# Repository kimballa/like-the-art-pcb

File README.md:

You Don't Have to Like All the Art! -- PCBs
===========================================

PCB designs and eCAD files for the "You Don't Have to Like All the Art!" project.

This system consists of two distinct circuit boards:

* `lta-logic-module` - The "logic" that determines when it's dark out / should be active, what
  messages to light up on the sign, manages PWM or other effects when displaying the sign, and
  also handles button inputs from users. Runs on a combination of 5V and 3V3. This is designed
  around a port for installing an Adafruit Feather M4 Express (ATSAMD51 / Cortex-M4) Arduino
  device. The rest of the circuitry:
  * Provides regulated 5V0 input voltage for the rest of this module
  * Manages a wide fanout of control and sense lines via I2C
  * Uses a phototransistor to sense when it is dark out, and thus the system should be active
    vs in standby mode
  * Combines the sign control lines with a global PWM signal and buffers the output before feeding
    to the power module.
* `lta-power-module` - The high-power circuits that actually drive the LED signs. This module is
  "dumb" and contains no combinational logic or more complex circuitry. Most of the board is used
  for mounting 3rd-party PCB submodules for high-amp 12V0 voltage regulation, distributing a
  power bus, and actually driving power MOSFETs linked to each sign's power wiring. The onboard
  circuitry:
  * Provides regulated 5V0 input voltage for the rest of the onboard circuitry
  * Displays condition of regulated 12V0 input power
  * Uses SN75374 low-side drivers to send control signals to the MOSFET modules
  * Contains a small integrated protoboard for in-field repairs and modifications

The `photodiode-sim` subproject is a simplified version of the `DARK` detection circuitry for use
with `ngspice` to understand the sensitivity of the logic signal to input current levels from the
phototransistor and the variable resistance of the potentiometer used as an in-field sensitivity
calibration input.

A third PCB (`mosfet-chip`) is a mini-PCB to connect two circuits via screw-terminals, switchable by
an onboard `IRLZ24` NMOS FET transistor activated by a separate gate pin. 16 of these are mounted on
the power module by #0 machine screws.

I originally used this
[High-Power Dual MOSFET Switch Module](https://protosupplies.com/product/high-power-dual-mosfet-switch-module/)
but found the screw terminals included were too unreliable. This PCB is footprint-compatible and
uses larger-gauge, higher-quality terminal blocks by Phoenix Contact. The `mosfet-chip/` directory
includes a panelized (2x3) layout suitable for PCBA and the BOM to enable assembly at JLCPCB.

Fabrication
-----------

All models are built with KiCAD 6. Each module contains a BOM spreadsheet for assembly with MPNs to
order from DigiKey or elsewhere as noted. Per-run fabrication gerbers are kept in versioned
subdirectories of each submodule project.

All modules are fabricated with the following parameters:

* 2 layers
* 1.6mm finished board thickness
* FR4-Tg130 core
* Both layers 1 oz copper thickness
* Blue soldermask, white silkscreen (these choices made only for aesthetic reasons and do not
  affect eng or mfg)

The logic module is fabricated with ENIG finish for reflow; the power module can be finished
with RoHS Pb-free HASL.

The logic module was fabricated by Elecrow and follows their design rules. Smallest
traces are 0.20mm. All trace separation >= 0.15mm.

The power module was fabricated by JLCPCB and follows their design rules. Smallest power module
traces and trace separations are 0.25mm / 0.20mm, which more than meets their capabilities.

Assembly
--------

Boards require only single-sided assembly.

The logic module is a mixed SMD/THT board and was assembled by Elecrow. Smallest reflow components
are 0603. Logic module ICs are SOIC (1.27mm pitch). Actual LEDs, resistors, and IC decoupling
capacitors do not follow the BOM strictly but instead use house parts (except as noted `Exact MPN
Only` in the BOM). More notes about logic module assembly are in `README-fab-and-pcba.txt` in
the logic module directory.

The power module is THT-only and intended for hand-soldered assembly. (A single 7343-metric / 2917
/ "size D" tantalum SMD capacitor for the 5V0 regulator can also be hand-soldered.)

The mosfet chips are a mixed SMD/THT assembly and were assembled by JLCPCB. BOM includes SPNs
for JLC's preferred supplier. Individual mini-PCBs are too small for automated SMD assembly,
so gerbers are supplied for a panelized 2x3 PCB layout, made with the Panelizer plugin for KiCAD 6.

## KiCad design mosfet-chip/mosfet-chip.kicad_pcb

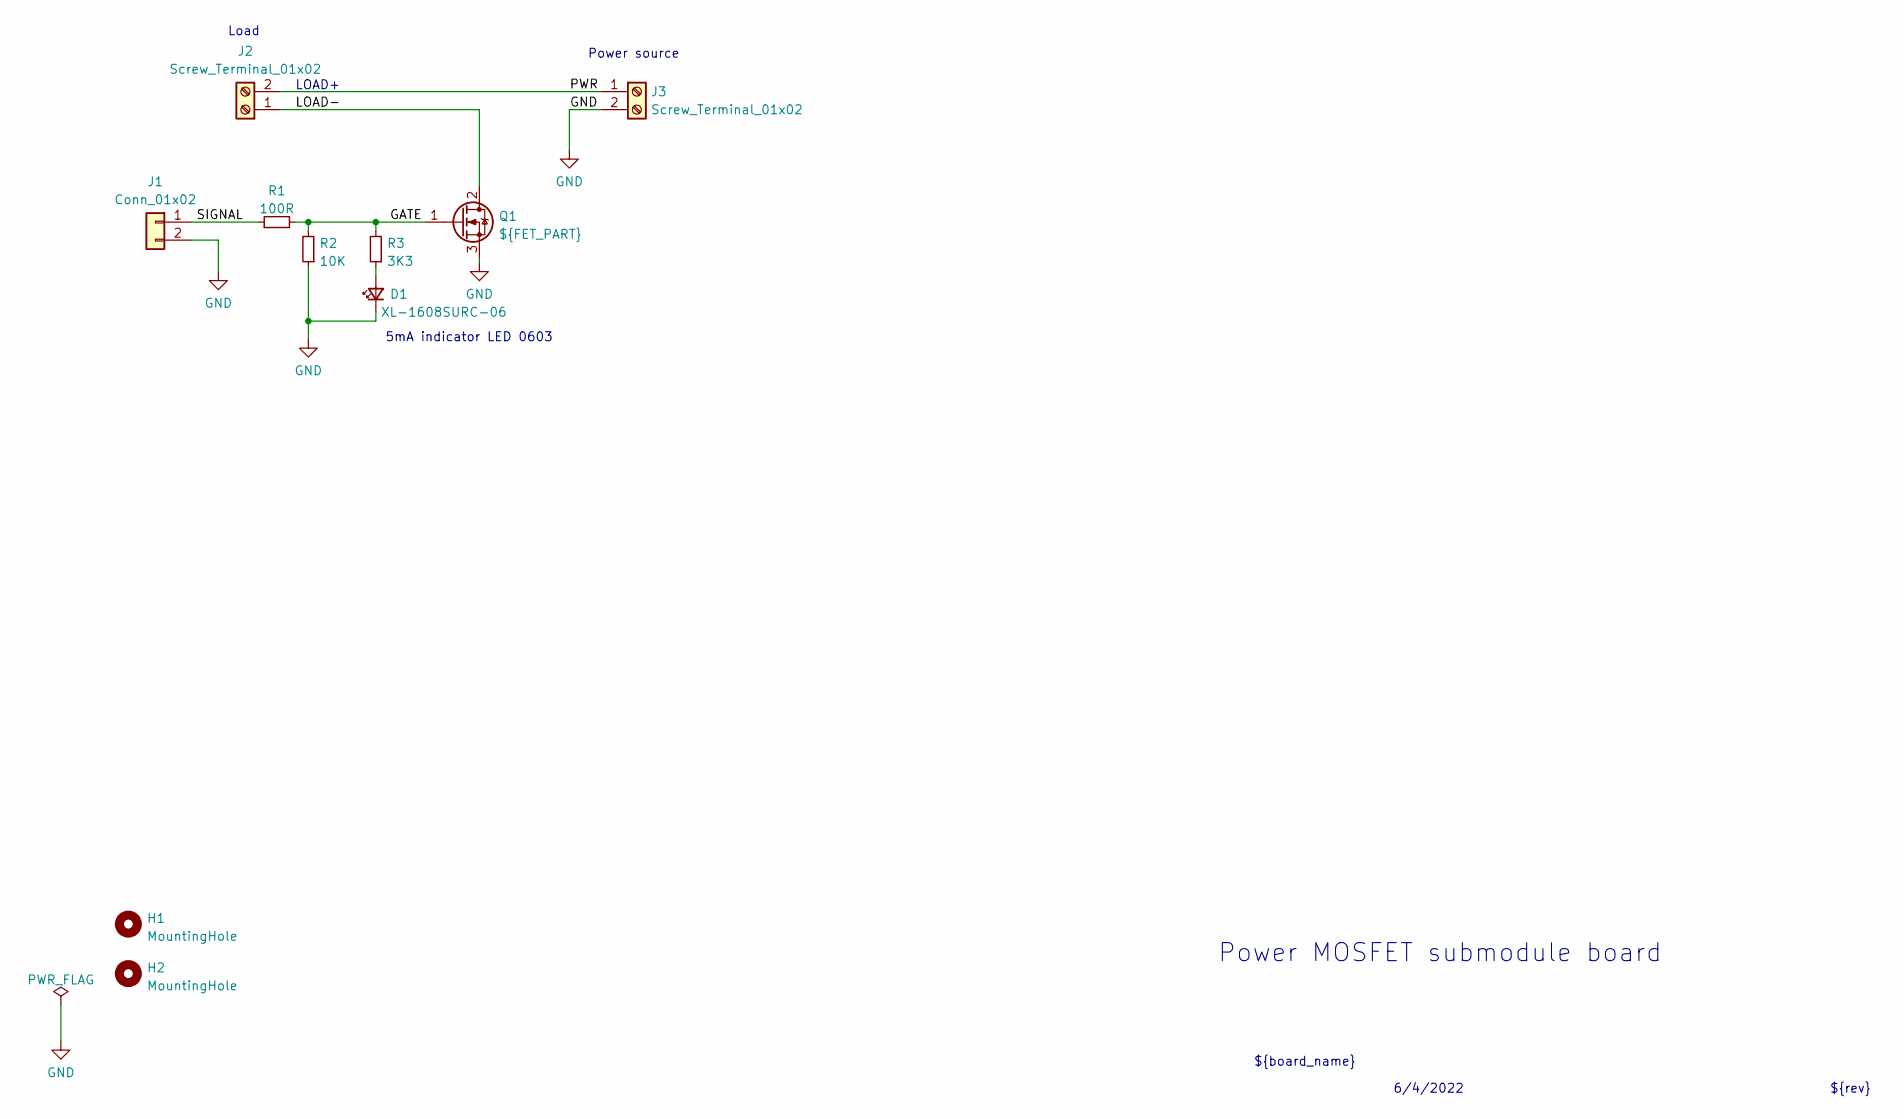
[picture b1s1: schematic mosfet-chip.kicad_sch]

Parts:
D1: XL-1608SURC-06; LED_0603_1608Metric; MPN XL-1608SURC-06; JLCPCB_PN C965799
H1, H2: MountingHole; MountingHole_80mil
J1: Conn_01x02; PinHeader_1x02_P2.54mm_Vertical; MPN 5-146858-1; JLCPCB_PN DNP
J2, J3: Screw_Terminal_01x02; Phoenix_1x02_1711725; MPN 1711725; JLCPCB_PN C89120
Q1: ${FET_PART}; TO-220-3_Vertical; MPN IRLZ34NPbF; JLCPCB_PN C513144
R1: 100R; R_0603_1608Metric; MPN 0603WAF1000T5E; JLCPCB_PN C22775
R2: 10K; R_0603_1608Metric; MPN 0603WAF1002T5E; JLCPCB_PN C25804
R3: 3K3; R_0603_1608Metric; MPN 0603WAF3301T5E; JLCPCB_PN C22978

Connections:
/GATE: Q1.1 (G), R1.2, R2.2, R3.2
/LOAD-: J2.1, Q1.2 (D)
/PWR: J2.2, J3.1
/SIGNAL: J1.1, R1.1
GND: D1.1 (K), J1.2, J3.2, Q1.3 (S), R2.1
unnamed: D1.2 (A), R3.1

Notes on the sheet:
Load
Power MOSFET submodule board
5mA indicator LED 0603
${rev}
LOAD+
${board_name}
6/4/2022
Power source

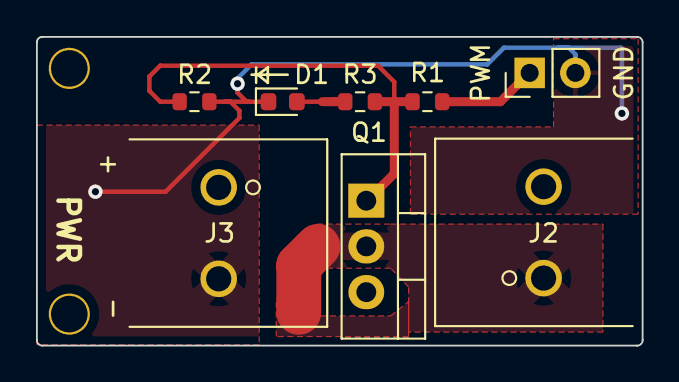
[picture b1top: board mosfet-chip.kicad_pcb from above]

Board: 2 copper layers, 33.6 x 17.1 mm, 10 parts (0 on the bottom side), 6 nets.

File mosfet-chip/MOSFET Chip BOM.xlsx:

Reference | Value | Footprint | Datasheet | Comment | JLCPCB_PN | MANUFACTURER | MPN | SPN | Qty
D1 | XL-1608SURC-06 | LED_SMD:LED_0603_1608Metric | https://datasheet.lcsc.com/lcsc/2012301032_XINGLIGHT-XL-1608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 |  | C965799 | XINGLIGHT | XL-1608SURC-06 |  | 1
> H1, H2 | MountingHole | Aaron_Pads:MountingHole_80mil | ~ |  |  |  |  |  | 2
J1 | Conn_01x02 | Connector_PinHeader_2.54mm:PinHeader_1x02_P2.54mm_Vertical | ~ | 0.1" gold male header pins | DNP | TE Connectivity AMP Connectors | 5-146858-1 | A105469CT-ND | 1
> J2, J3 | Screw_Terminal_01x02 | Aaron_Phoenix_Parts:Phoenix_1x02_1711725 | https://media.digikey.com/pdf/Data%20Sheets/Phoenix%20Contac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 |  | C89120 | Phoenix Contact | 1711725 | 277-1027-ND | 2
Q1 | ${FET_PART} | Package_TO_SOT_THT:TO-220-3_Vertical | https://www.infineon.com/dgdl/irlz34npbf.pdf?fileId=5546d462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 |  | C513144 | Infineon | IRLZ34NPbF | IRLZ34NPBF-ND | 1
R1 | 100R | Resistor_SMD:R_0603_1608Metric |  | 100R 1% 1/10W | C22775 | UNI-ROYAL | 0603WAF1000T5E |  | 1
R2 | 10K | Resistor_SMD:R_0603_1608Metric |  | 10K 1% 1/10W | C25804 | UNI-ROYAL | 0603WAF1002T5E |  | 1
R3 | 3K3 | Resistor_SMD:R_0603_1608Metric |  | 3K3 1% 1/10W | C22978 | UNI-ROYAL | 0603WAF3301T5E |  | 1

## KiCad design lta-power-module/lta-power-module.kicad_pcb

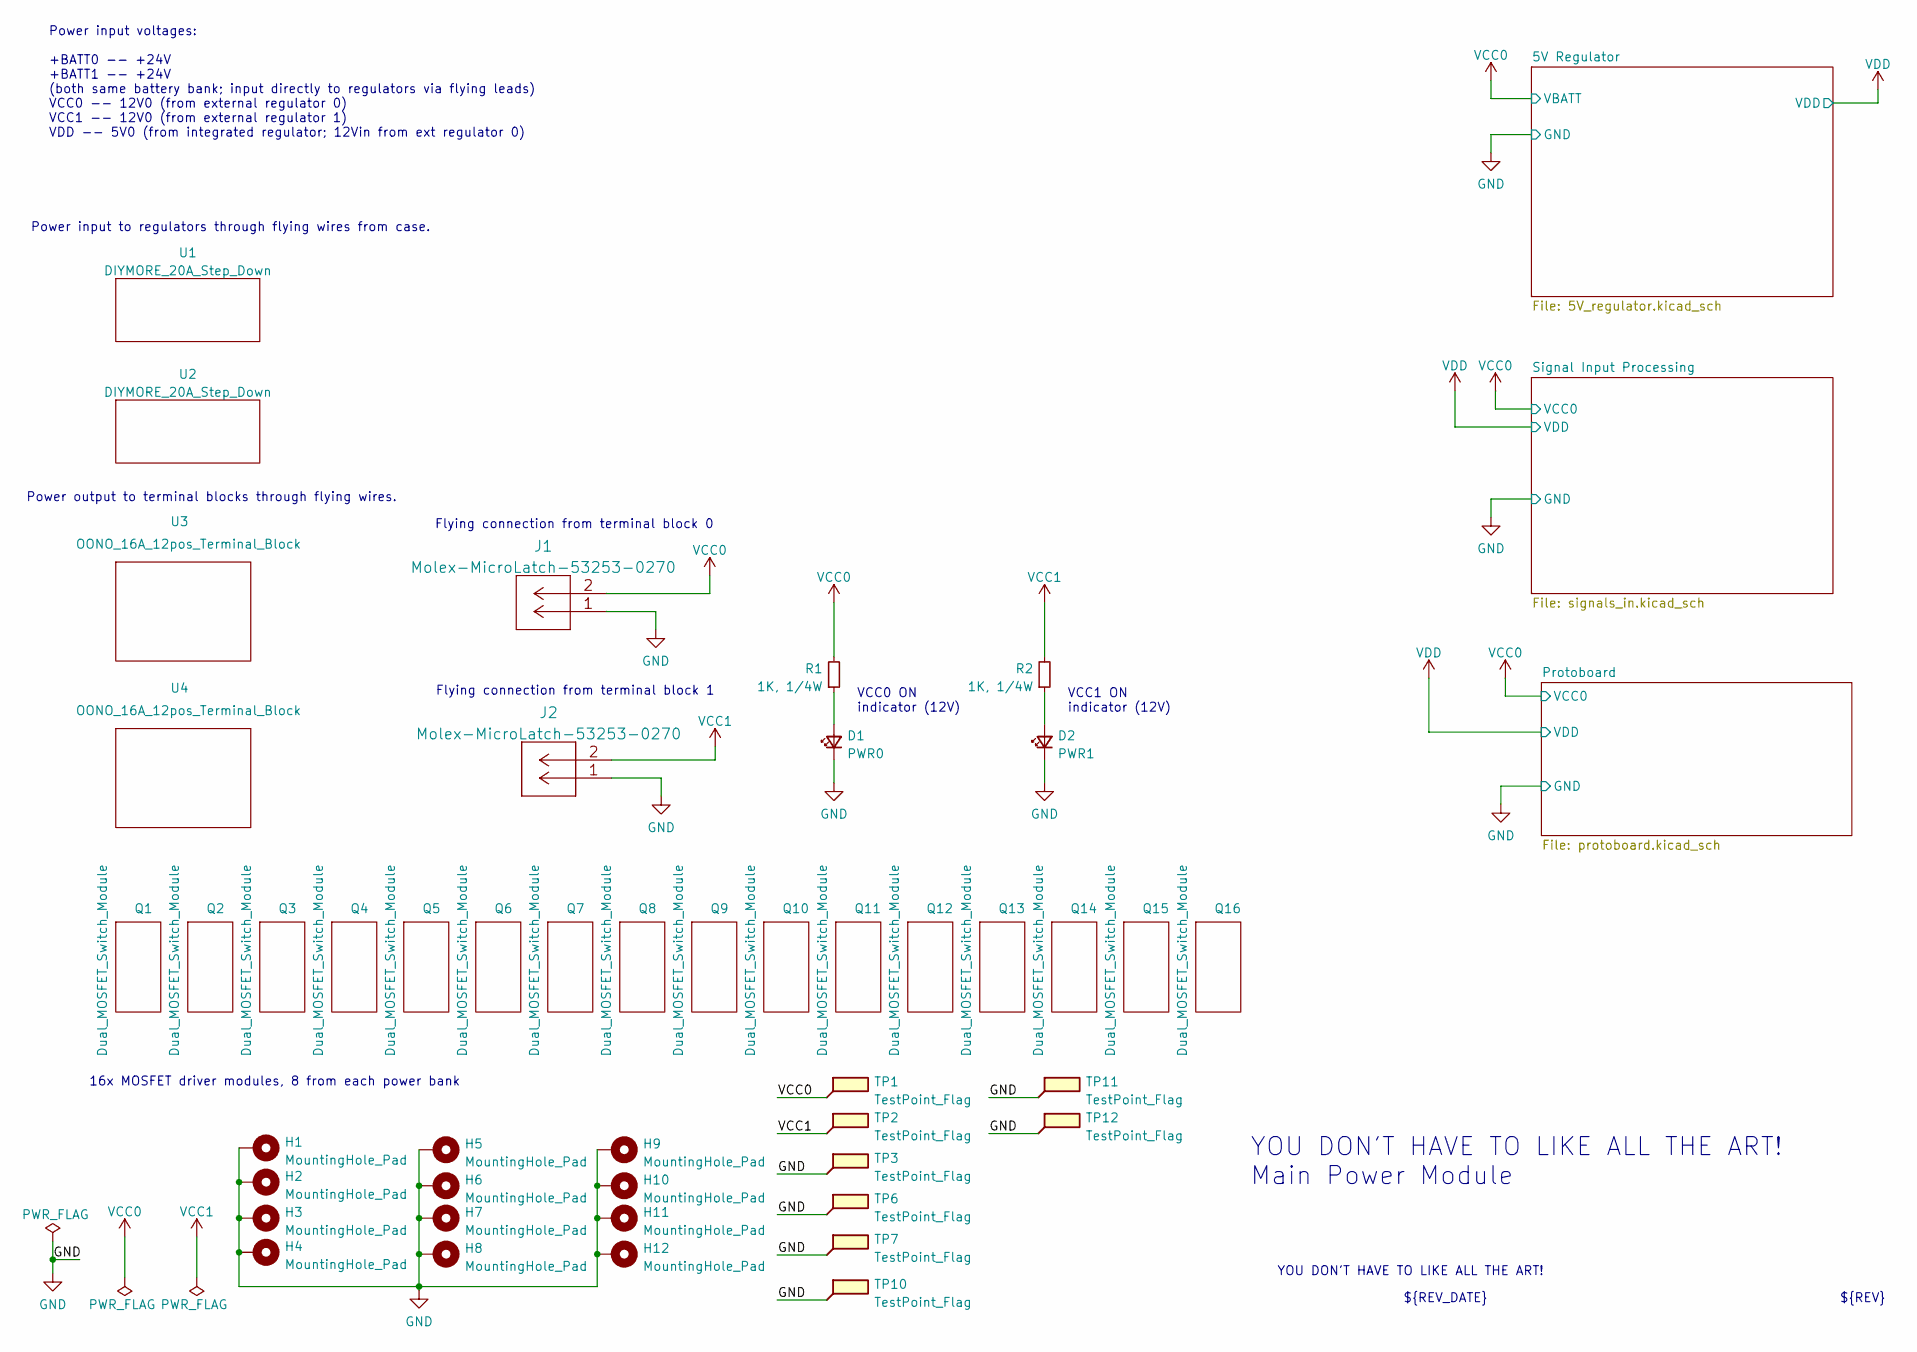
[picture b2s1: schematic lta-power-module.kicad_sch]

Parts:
D1: PWR0; LED_D5.0mm_SilkFix; MPN C5SMF-RJF-CT0W0BB1
D2: PWR1; LED_D5.0mm_SilkFix; MPN C5SMF-RJF-CT0W0BB1
H1, H2, H3, H4, H5, H6, H7, H8, H9, H10, H11, H12: MountingHole_Pad; MountingHole_5.3mm_M5_ISO7380_Pad
J1, J2: Molex-MicroLatch-53253-0270; MPN 532530270
Q1, Q2, Q3, Q4, Q5, Q6, Q7, Q8, Q9, Q10, Q11, Q12, Q13, Q14, Q15, Q16: Dual_MOSFET_Switch_Module; Dual_MOSFET_Driver
R1, R2: 1K, 1/4W; R_Axial_DIN0207_L6.3mm_D2.5mm_P7.62mm_Horizontal; MPN CF14JT1K00
TP1, TP2, TP3, TP6, TP7, TP10, TP11, TP12: TestPoint_Flag; TestPoint_THTPad_1.0x1.0mm_Drill0.3mm
U1, U2: DIYMORE_20A_Step_Down; 12V_regulator
U3, U4: OONO_16A_12pos_Terminal_Block; 12-way_power_distribution_bus

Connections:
GND: D1.1 (K), D2.1 (K), H1.1, H2.1, H3.1, H4.1, H5.1, H6.1, H7.1, H8.1, H9.1, H10.1, H11.1, H12.1, J1.1, J2.1, TP3.1, TP6.1, TP7.1, TP10.1, TP11.1, TP12.1; also elsewhere on the board
unnamed: D1.2 (A), R1.1
unnamed: D2.2 (A), R2.1
VCC0: J1.2, R1.2, TP1.1; also elsewhere on the board
VCC1: J2.2, R2.2, TP2.1

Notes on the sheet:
${REV}
VCC1 ON indicator (12V)
Flying connection from terminal block 0
Power output to terminal blocks through flying wires.
Power input to regulators through flying wires from case.
YOU DON'T HAVE TO LIKE ALL THE ART!
YOU DON'T HAVE TO LIKE ALL THE ART! Main Power Module
16x MOSFET driver modules, 8 from each power bank
VCC0 ON indicator (12V)
Power input voltages: +BATT0 -- +24V +BATT1 -- +24V (both same battery bank; input directly to regulators via flying leads) VCC0 -- 12V0 (from external regulator 0) VCC1 -- 12V0 (from external regulator 1) VDD -- 5V0 (from integrated regulator; 12Vin from ext regulator 0)
Flying connection from terminal block 1
${REV_DATE}

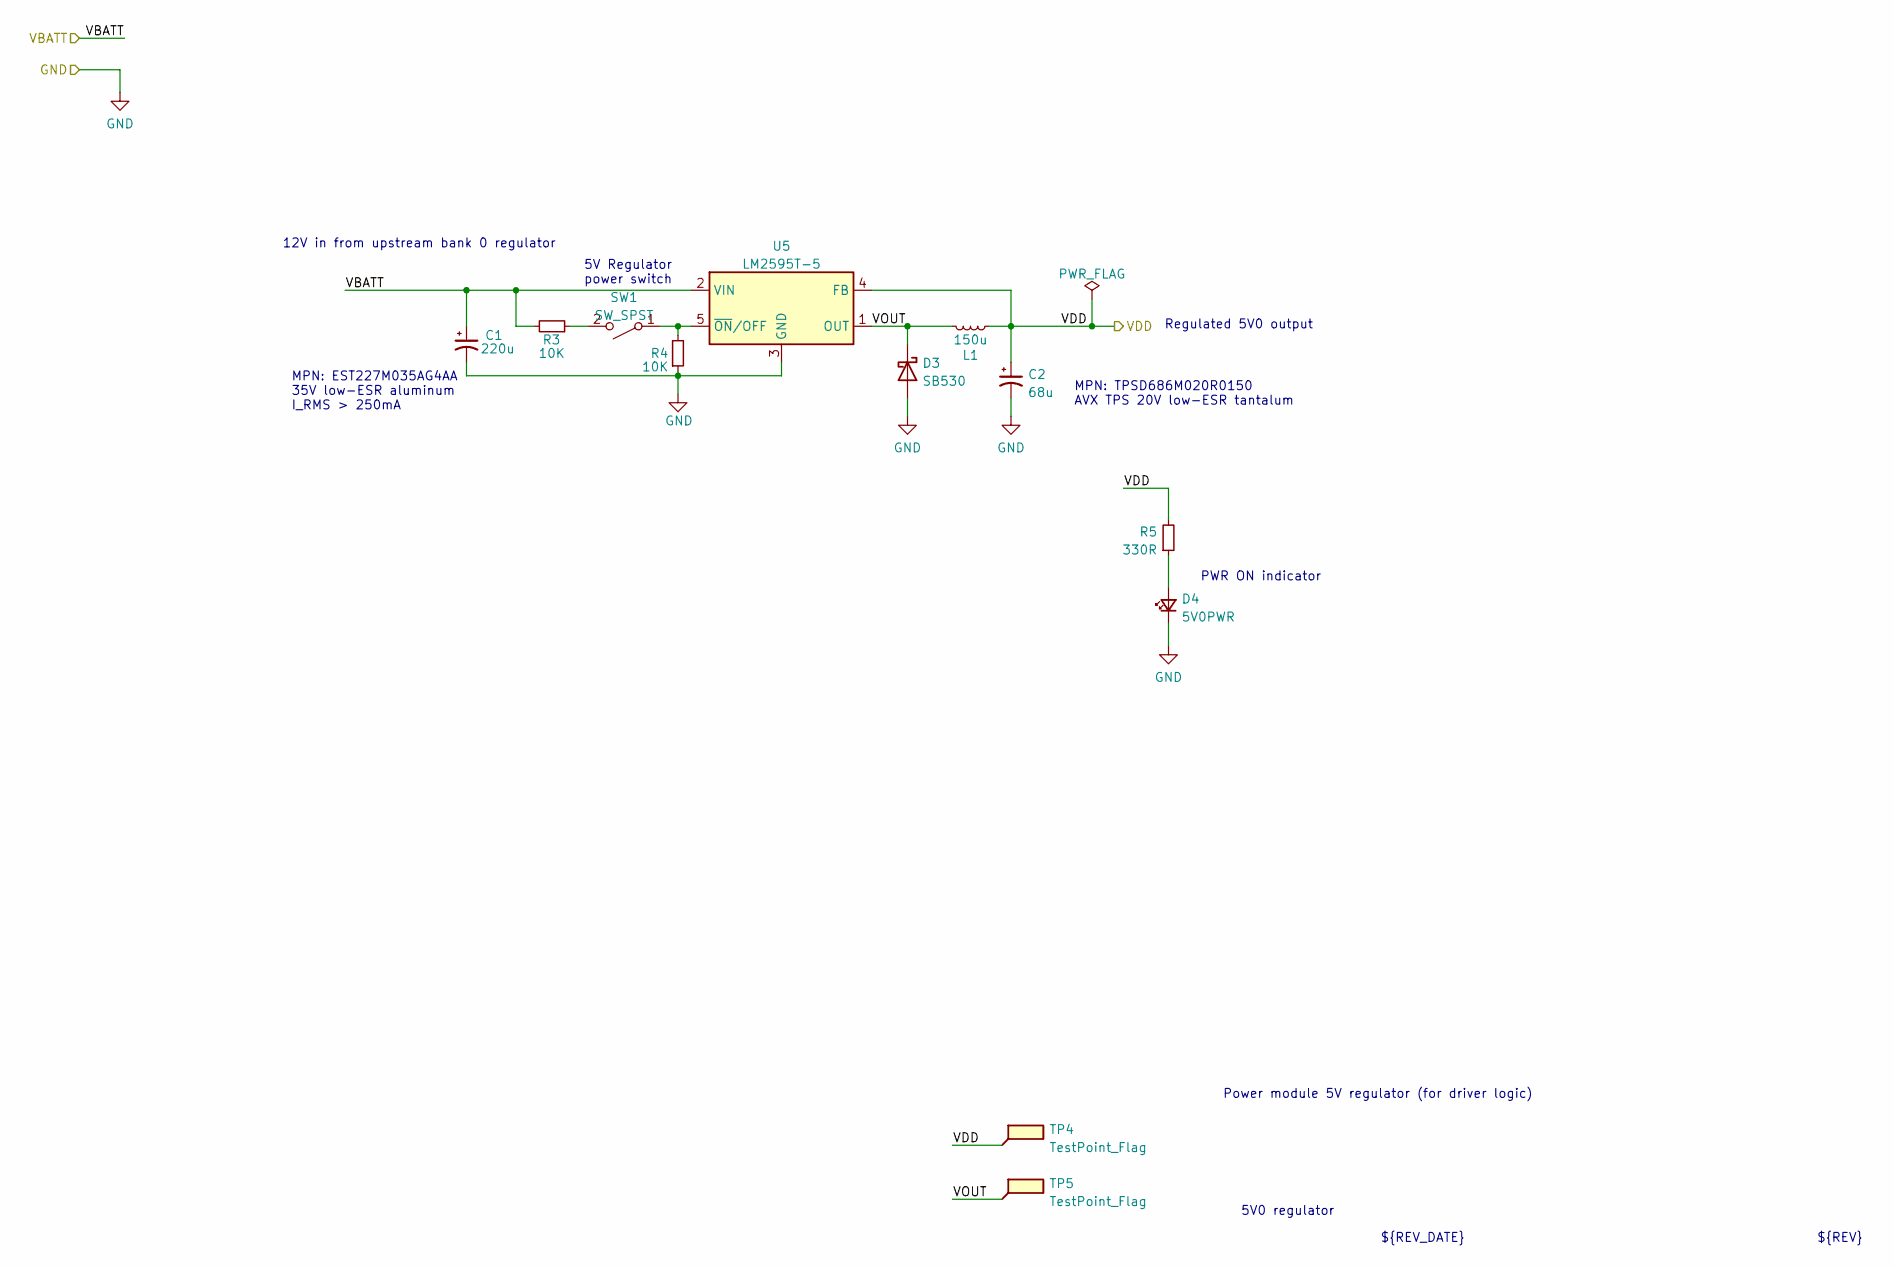
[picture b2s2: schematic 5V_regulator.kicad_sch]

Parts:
C1: 220u; CP_Radial_D8.0mm_P3.50mm; MPN EST227M035AG4AA
C2: 68u; CP_EIA-7343-30_AVX-N_Pad2.25x2.55mm_HandSolder; MPN TPSD686M020R0150
D3: SB530; D_DO-201AD_P15.24mm_Horizontal; MPN SB530-E3/54
D4: 5V0PWR; LED_D5.0mm_SilkFix; MPN C5SMF-RJF-CT0W0BB1
L1: 150u; L_Radial_D13.5mm_P7.50mm; MPN AIUR-06-151K
R3, R4: 10K; R_Axial_DIN0204_L3.6mm_D1.6mm_P5.08mm_Horizontal; MPN CF18JT10K0
R5: 330R; R_Axial_DIN0204_L3.6mm_D1.6mm_P5.08mm_Horizontal; MPN CF18JT330R
SW1: SW_SPST; CUI-DIP-SW_DS01-254-x-01xx; MPN DS01-254-S-01BE
TP4, TP5: TestPoint_Flag; TestPoint_THTPad_1.0x1.0mm_Drill0.3mm
U5: LM2595T-5; TO-220-5_P3.4x3.7mm_StaggerOdd_Lead3.8mm_Vertical-SilkFix; MPN LM2595T-5.0/NOPB

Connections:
/5V Regulator/VOUT: D3.1 (K), L1.2, TP5.1, U5.1 (OUT)
GND: C1.2, C2.2, D3.2 (A), D4.1 (K), R4.1, U5.3 (GND); also elsewhere on the board
unnamed: D4.2 (A), R5.1
unnamed: R3.1, SW1.2 (B)
unnamed: R4.2, SW1.1 (A), U5.5 (~ON/OFF)
VCC0: C1.1, R3.2, U5.2 (VIN); also elsewhere on the board
VDD: C2.1, L1.1, R5.2, TP4.1, U5.4 (FB); also elsewhere on the board

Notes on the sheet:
MPN: TPSD686M020R0150 AVX TPS 20V low-ESR tantalum
12V in from upstream bank 0 regulator
Power module 5V regulator (for driver logic)
MPN: EST227M035AG4AA 35V low-ESR aluminum I_RMS > 250mA
${REV}
Regulated 5V0 output
5V0 regulator
5V Regulator power switch
${REV_DATE}
PWR ON indicator

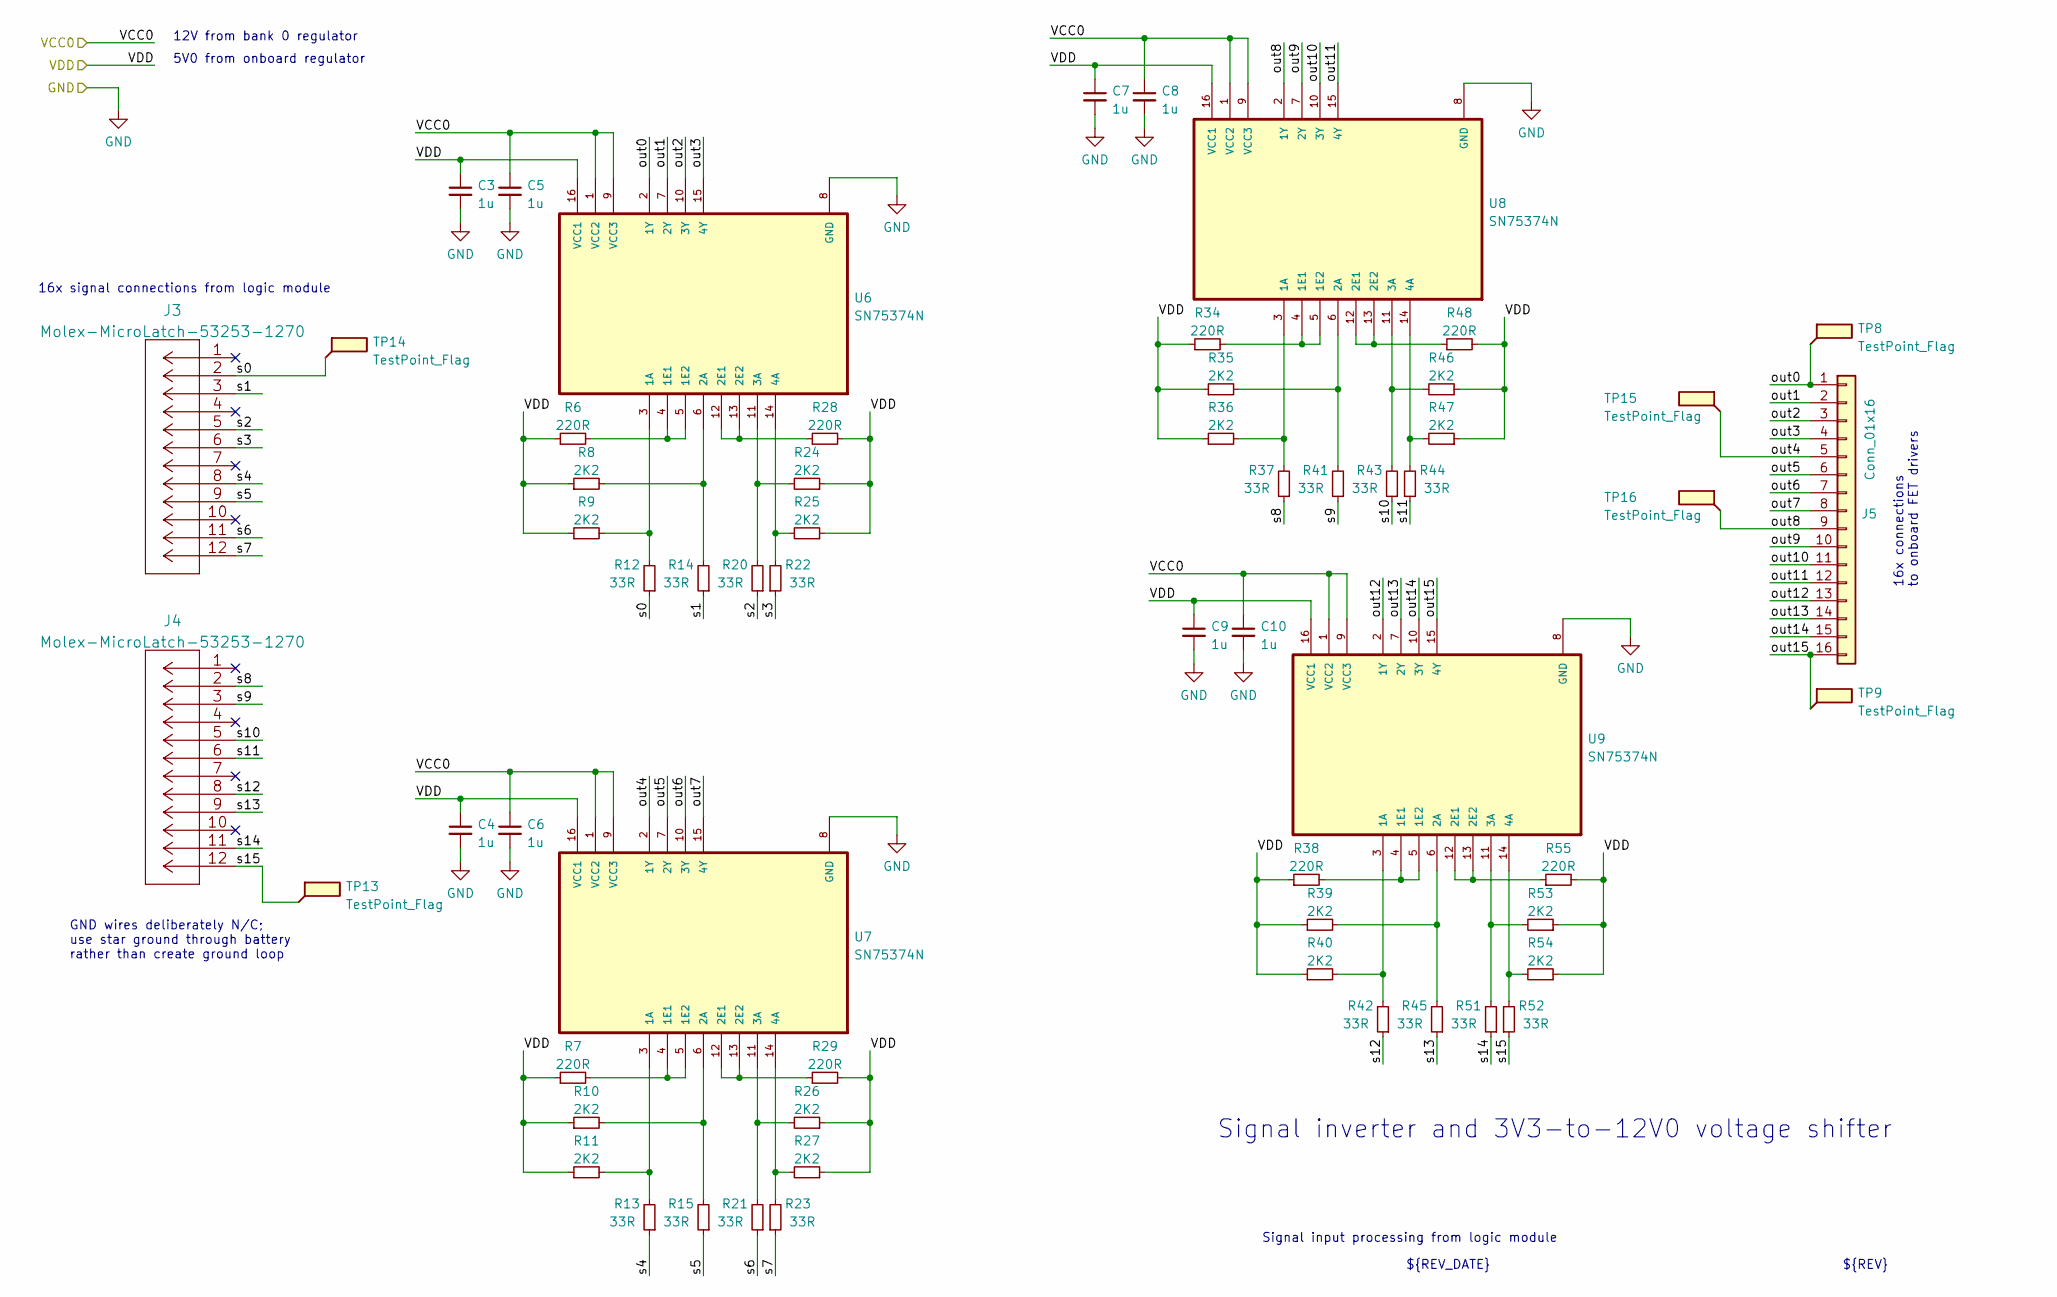
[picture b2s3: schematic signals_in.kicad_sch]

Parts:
C3, C4, C5, C6, C7, C8, C9, C10: 1u; C_Disc_D3.8mm_W2.6mm_P2.50mm; MPN C315C105K3R5TA7303
J3, J4: Molex-MicroLatch-53253-1270; MPN 532531270
J5: Conn_01x16; PinHeader_1x16_P2.54mm_Vertical; MPN 5-146858-1
R6, R7, R28, R29, R34, R38, R48, R55: 220R; R_Axial_DIN0204_L3.6mm_D1.6mm_P5.08mm_Horizontal; MPN CF18JT220R
R8, R9, R10, R11, R24, R25, R26, R27, R35, R36, R39, R40, R46, R47, R53, R54: 2K2; R_Axial_DIN0204_L3.6mm_D1.6mm_P5.08mm_Horizontal; MPN CF18JT2K20
R12, R13, R14, R15, R20, R21, R22, R23, R37, R41, R42, R43, R44, R45, R51, R52: 33R; R_Axial_DIN0204_L3.6mm_D1.6mm_P5.08mm_Horizontal; MPN CF18JT33R0
TP8, TP9, TP13, TP14, TP15, TP16: TestPoint_Flag; TestPoint_THTPad_1.0x1.0mm_Drill0.3mm
U6, U7, U8, U9: SN75374N; TI_N_R-PDIP-T16; MPN SN75374N

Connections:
/Signal Input Processing/out0: J5.1, TP8.1, U6.2 (1Y)
/Signal Input Processing/out1: J5.2, U6.7 (2Y)
/Signal Input Processing/out2: J5.3, U6.10 (3Y)
/Signal Input Processing/out3: J5.4, U6.15 (4Y)
/Signal Input Processing/out4: J5.5, TP15.1, U7.2 (1Y)
/Signal Input Processing/out5: J5.6, U7.7 (2Y)
/Signal Input Processing/out6: J5.7, U7.10 (3Y)
/Signal Input Processing/out7: J5.8, U7.15 (4Y)
/Signal Input Processing/out8: J5.9, TP16.1, U8.2 (1Y)
/Signal Input Processing/out9: J5.10, U8.7 (2Y)
/Signal Input Processing/out10: J5.11, U8.10 (3Y)
/Signal Input Processing/out11: J5.12, U8.15 (4Y)
/Signal Input Processing/out12: J5.13, U9.2 (1Y)
/Signal Input Processing/out13: J5.14, U9.7 (2Y)
/Signal Input Processing/out14: J5.15, U9.10 (3Y)
/Signal Input Processing/out15: J5.16, TP9.1, U9.15 (4Y)
/Signal Input Processing/s0: J3.2, R12.1, TP14.1
/Signal Input Processing/s1: J3.3, R14.1
/Signal Input Processing/s2: J3.5, R20.1
/Signal Input Processing/s3: J3.6, R22.1
/Signal Input Processing/s4: J3.8, R13.1
/Signal Input Processing/s5: J3.9, R15.1
/Signal Input Processing/s6: J3.11, R21.1
/Signal Input Processing/s7: J3.12, R23.1
/Signal Input Processing/s8: J4.2, R37.1
/Signal Input Processing/s9: J4.3, R41.1
/Signal Input Processing/s10: J4.5, R43.1
/Signal Input Processing/s11: J4.6, R44.1
/Signal Input Processing/s12: J4.8, R42.1
/Signal Input Processing/s13: J4.9, R45.1
/Signal Input Processing/s14: J4.11, R51.1
/Signal Input Processing/s15: J4.12, R52.1, TP13.1
GND: C3.2, C4.2, C5.2, C6.2, C7.2, C8.2, C9.2, C10.2, U6.8 (GND), U7.8 (GND), U8.8 (GND), U9.8 (GND); also elsewhere on the board
unnamed: R6.2, U6.4 (1E1), U6.5 (1E2)
unnamed: R7.2, U7.4 (1E1), U7.5 (1E2)
unnamed: R10.2, R15.2, U7.6 (2A)
unnamed: R11.2, R13.2, U7.3 (1A)
unnamed: R9.2, R12.2, U6.3 (1A)
unnamed: R8.2, R14.2, U6.6 (2A)
unnamed: R20.2, R24.2, U6.11 (3A)
unnamed: R21.2, R26.2, U7.11 (3A)
unnamed: R22.2, R25.2, U6.14 (4A)
unnamed: R23.2, R27.2, U7.14 (4A)
unnamed: R28.1, U6.12 (2E1), U6.13 (2E2)
unnamed: R29.1, U7.12 (2E1), U7.13 (2E2)
unnamed: R34.2, U8.4 (1E1), U8.5 (1E2)
unnamed: R35.2, R41.2, U8.6 (2A)
unnamed: R36.2, R37.2, U8.3 (1A)
unnamed: R38.2, U9.4 (1E1), U9.5 (1E2)
unnamed: R39.2, R45.2, U9.6 (2A)
unnamed: R40.2, R42.2, U9.3 (1A)
unnamed: R43.2, R46.2, U8.11 (3A)
unnamed: R44.2, R47.2, U8.14 (4A)
unnamed: R48.1, U8.12 (2E1), U8.13 (2E2)
unnamed: R51.2, R53.2, U9.11 (3A)
unnamed: R52.2, R54.2, U9.14 (4A)
unnamed: R55.1, U9.12 (2E1), U9.13 (2E2)
VCC0: C5.1, C6.1, C8.1, C10.1, U6.1 (VCC2), U6.9 (VCC3), U7.1 (VCC2), U7.9 (VCC3), U8.1 (VCC2), U8.9 (VCC3), U9.1 (VCC2), U9.9 (VCC3); also elsewhere on the board
VDD: C3.1, C4.1, C7.1, C9.1, R6.1, R7.1, R8.1, R9.1, R10.1, R11.1, R24.1, R25.1, R26.1, R27.1, R28.2, R29.2, R34.1, R35.1, R36.1, R38.1, R39.1, R40.1, R46.1, R47.1, R48.2, R53.1, R54.1, R55.2, U6.16 (VCC1), U7.16 (VCC1), U8.16 (VCC1), U9.16 (VCC1); also elsewhere on the board

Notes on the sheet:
16x connections to onboard FET drivers
${REV}
GND wires deliberately N/C; use star ground through battery rather than create ground loop
Signal inverter and 3V3-to-12V0 voltage shifter
12V from bank 0 regulator
16x signal connections from logic module
5V0 from onboard regulator
Signal input processing from logic module
${REV_DATE}

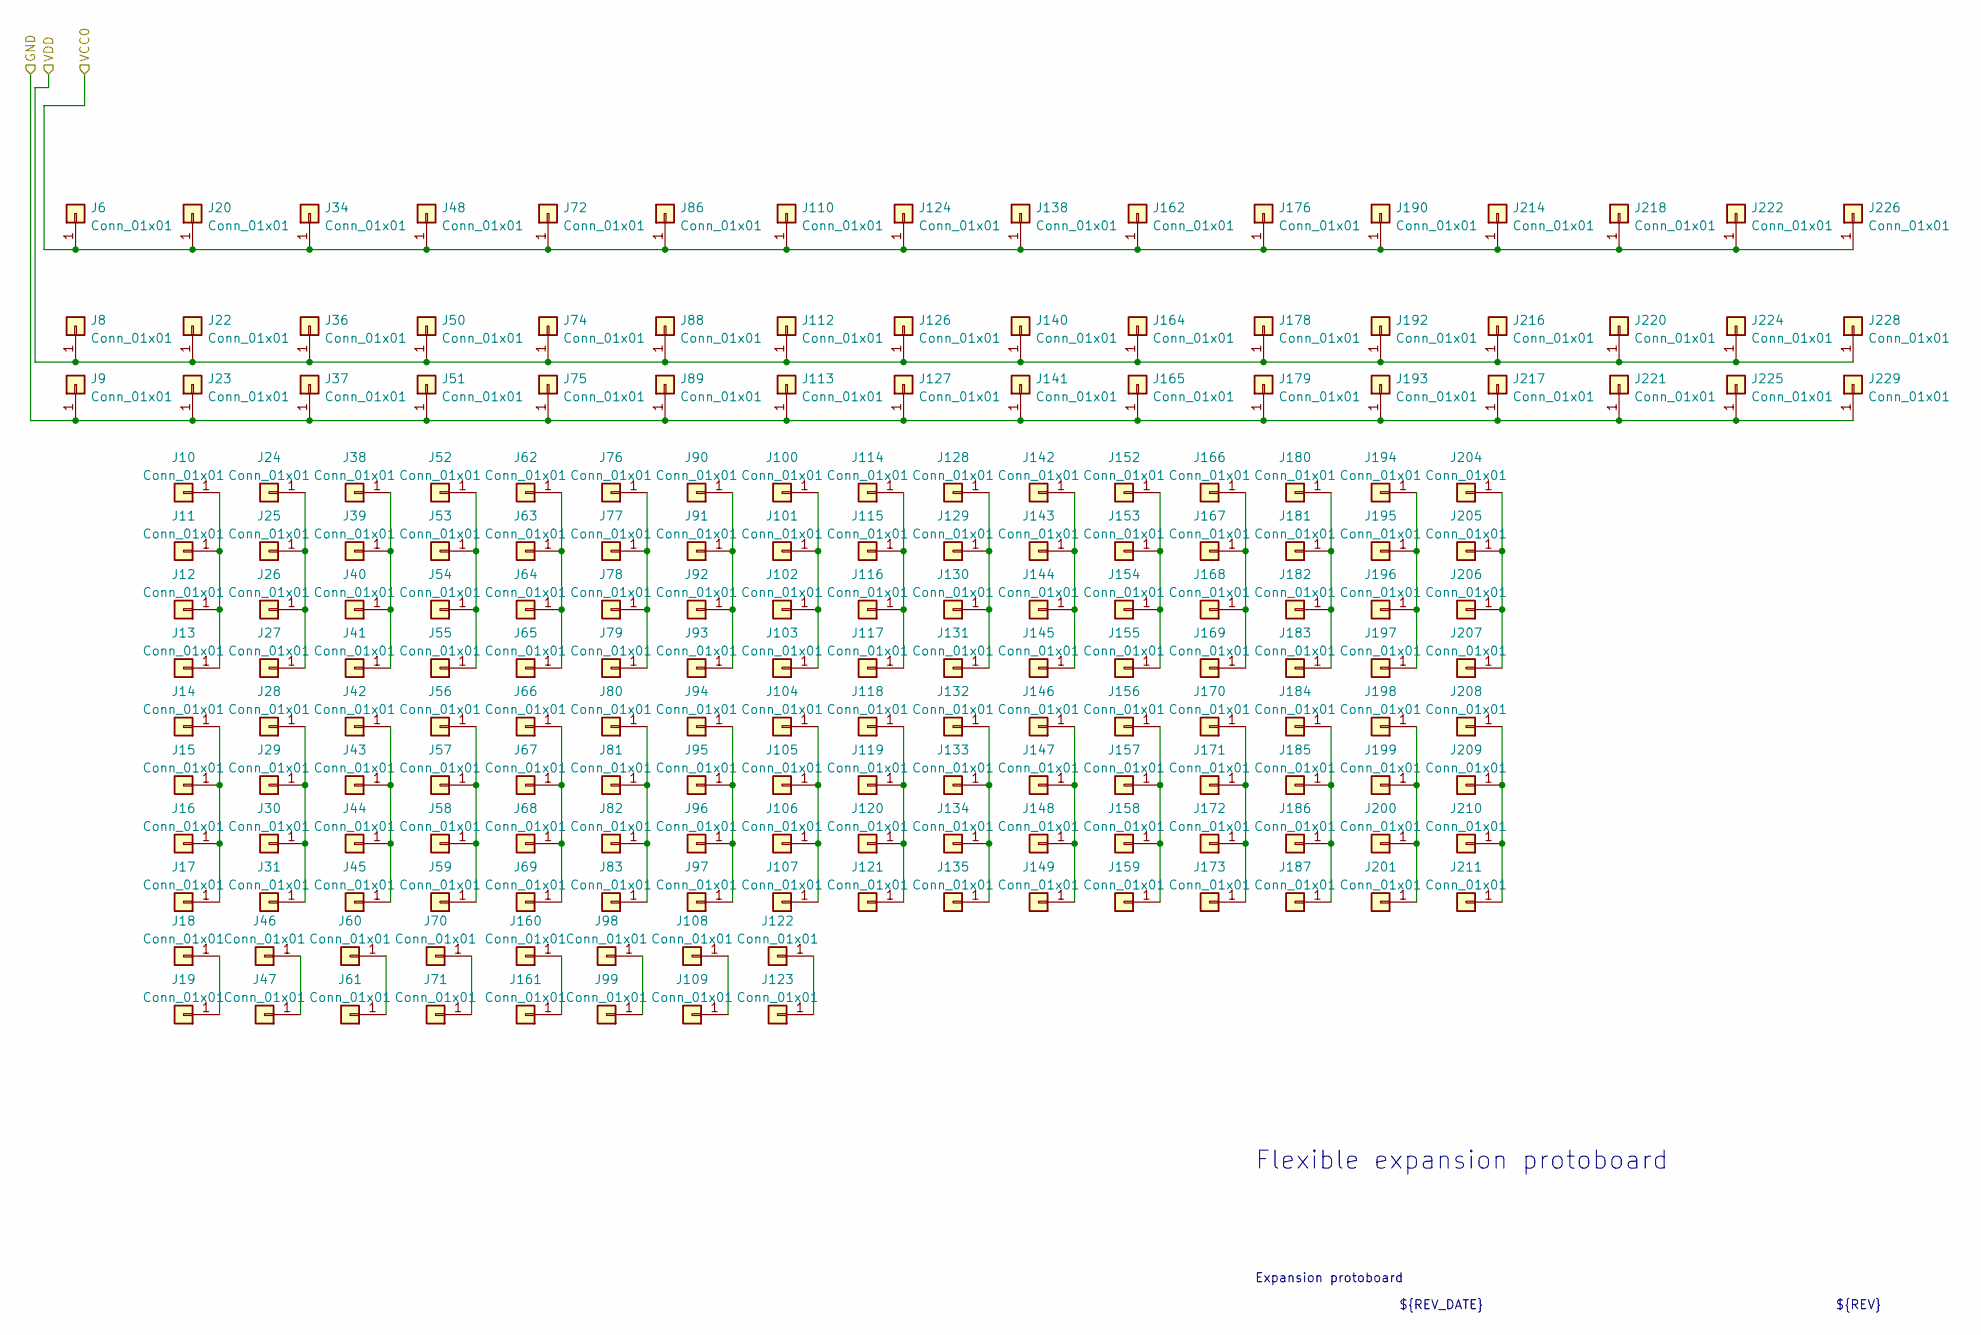
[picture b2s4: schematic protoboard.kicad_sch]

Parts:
J6, J8, J9, J10, J11, J12, J13, J14, J15, J16, J17, J19, J20, J22, J23, J24, J25, J26, J27, J28, J29, J30, J31, J34, J36, J37, J38, J39, J40, J41, J42, J43, J44, J45, J47, J48, J50, J51, J52, J53, J54, J55, J56, J57, J58, J59, J61, J62, J63, J64, J65, J66, J67, J68, J69, J71, J72, J74, J75, J76, J77, J78, J79, J80, J81, J82, J83, J86, J88, J89, J90, J91, J92, J93, J94, J95, J96, J97, J99, J100, J101, J102, J103, J104, J105, J106, J107, J109, J110, J112, J113, J114, J115, J116, J117, J118, J119, J120, J121, J123, J124, J126, J127, J128, J129, J130, J131, J132, J133, J134, J135, J138, J140, J141, J142, J143, J144, J145, J146, J147, J148, J149, J152, J153, J154, J155, J156, J157, J158, J159, J161, J162, J164, J165, J166, J167, J168, J169, J170, J171, J172, J173, J176, J178, J179, J180, J181, J182, J183, J184, J185, J186, J187, J190, J192, J193, J194, J195, J196, J197, J198, J199, J200, J201, J204, J205, J206, J207, J208, J209, J210, J211, J214, J216, J217, J218, J220, J221, J222, J224, J225, J226, J228, J229: Conn_01x01; 1mm_PTH_No_Silk
J18, J46, J60, J70, J98, J108, J122, J160: Conn_01x01; 1.6mm_PTH_No_Silk

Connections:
GND: J9.1, J23.1, J37.1, J51.1, J75.1, J89.1, J113.1, J127.1, J141.1, J165.1, J179.1, J193.1, J217.1, J221.1, J225.1, J229.1; also elsewhere on the board
unnamed: J10.1, J11.1, J12.1, J13.1
unnamed: J14.1, J15.1, J16.1, J17.1
unnamed: J18.1, J19.1
unnamed: J24.1, J25.1, J26.1, J27.1
unnamed: J28.1, J29.1, J30.1, J31.1
unnamed: J38.1, J39.1, J40.1, J41.1
unnamed: J42.1, J43.1, J44.1, J45.1
unnamed: J46.1, J47.1
unnamed: J52.1, J53.1, J54.1, J55.1
unnamed: J56.1, J57.1, J58.1, J59.1
unnamed: J60.1, J61.1
unnamed: J62.1, J63.1, J64.1, J65.1
unnamed: J66.1, J67.1, J68.1, J69.1
unnamed: J70.1, J71.1
unnamed: J76.1, J77.1, J78.1, J79.1
unnamed: J80.1, J81.1, J82.1, J83.1
unnamed: J90.1, J91.1, J92.1, J93.1
unnamed: J94.1, J95.1, J96.1, J97.1
unnamed: J98.1, J99.1
unnamed: J100.1, J101.1, J102.1, J103.1
unnamed: J104.1, J105.1, J106.1, J107.1
unnamed: J108.1, J109.1
unnamed: J114.1, J115.1, J116.1, J117.1
unnamed: J118.1, J119.1, J120.1, J121.1
unnamed: J122.1, J123.1
unnamed: J128.1, J129.1, J130.1, J131.1
unnamed: J132.1, J133.1, J134.1, J135.1
unnamed: J142.1, J143.1, J144.1, J145.1
unnamed: J146.1, J147.1, J148.1, J149.1
unnamed: J152.1, J153.1, J154.1, J155.1
unnamed: J156.1, J157.1, J158.1, J159.1
unnamed: J160.1, J161.1
unnamed: J166.1, J167.1, J168.1, J169.1
unnamed: J170.1, J171.1, J172.1, J173.1
unnamed: J180.1, J181.1, J182.1, J183.1
unnamed: J184.1, J185.1, J186.1, J187.1
unnamed: J194.1, J195.1, J196.1, J197.1
unnamed: J198.1, J199.1, J200.1, J201.1
unnamed: J204.1, J205.1, J206.1, J207.1
unnamed: J208.1, J209.1, J210.1, J211.1
VCC0: J6.1, J20.1, J34.1, J48.1, J72.1, J86.1, J110.1, J124.1, J138.1, J162.1, J176.1, J190.1, J214.1, J218.1, J222.1, J226.1; also elsewhere on the board
VDD: J8.1, J22.1, J36.1, J50.1, J74.1, J88.1, J112.1, J126.1, J140.1, J164.1, J178.1, J192.1, J216.1, J220.1, J224.1, J228.1; also elsewhere on the board

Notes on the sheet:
Expansion protoboard
${REV}
Flexible expansion protoboard
${REV_DATE}

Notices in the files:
parts and their libraries:
Copyright 2021 Accelerated Designs. All rights reserved.
